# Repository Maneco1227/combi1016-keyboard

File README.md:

# Combi1016-keyboard
Combi1016 keyboard is an additional keyboard, suitable for inputting hexadecimal number.
This keyboard is useful to input a css color code and coordinates on a cad application. 

In this repository, KiCAD schema, PCB layout, gerber and qmk firmware are available.
Their data is **AS IS**, no warranties.

# Key layout
Press Fn key, it changes Normal and Fn(Hex) mode alternately.

## Normal mode

## Fn(Hex) mode

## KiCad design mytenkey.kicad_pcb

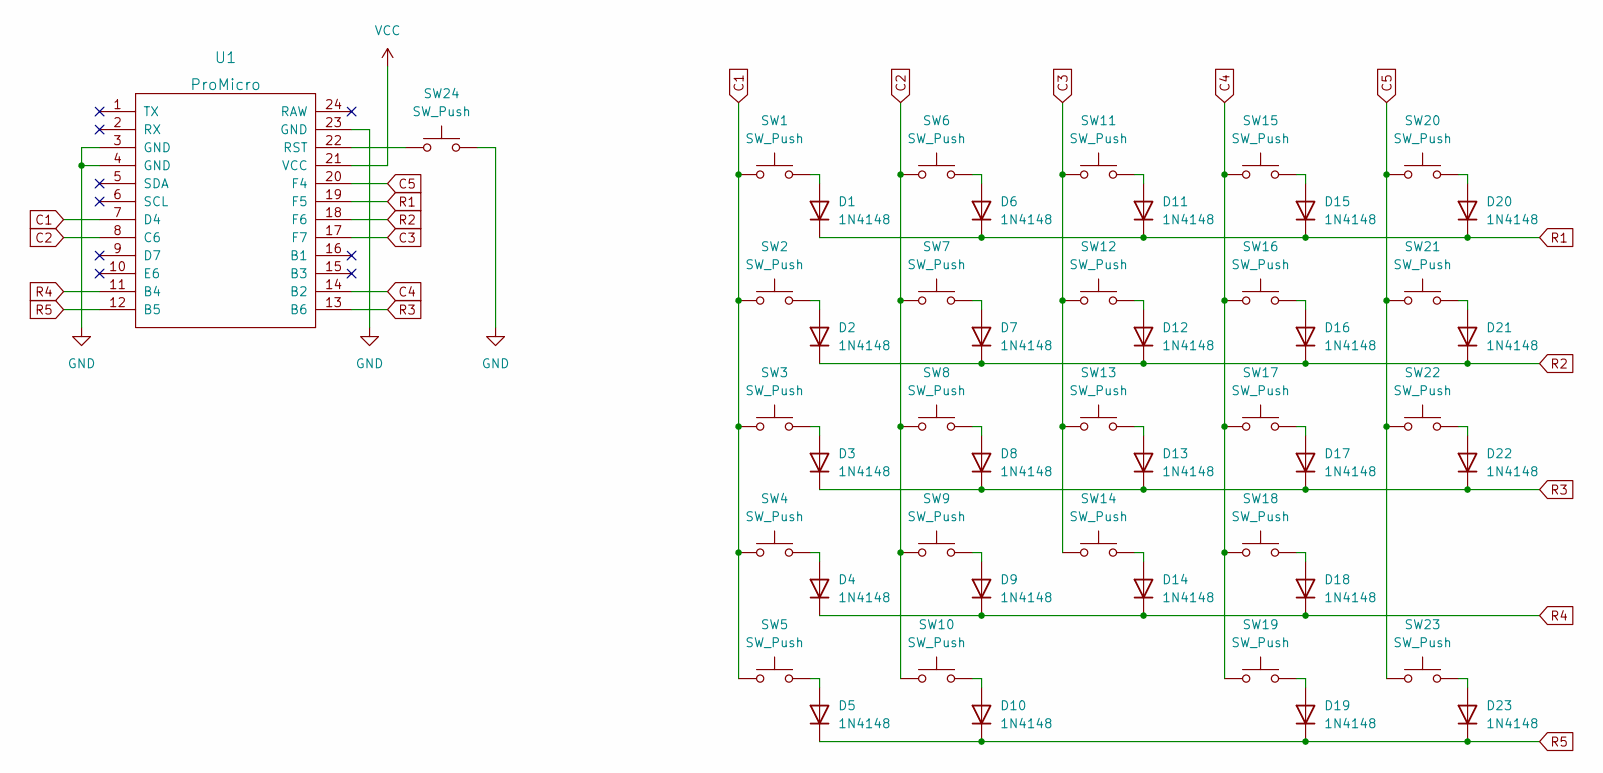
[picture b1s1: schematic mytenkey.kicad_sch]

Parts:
D1, D2, D3, D4, D5, D6, D7, D8, D9, D10, D11, D12, D13, D14, D15, D16, D17, D18, D19, D20, D21, D22, D23: 1N4148; D_DO-35_SOD27_P7.62mm_Horizontal
SW1, SW2, SW3, SW4, SW5, SW6, SW7, SW8, SW9, SW11, SW12, SW13, SW14, SW15, SW16, SW17, SW18, SW19, SW20, SW21, SW22: SW_Push; SW_Cherry_MX_1.00u_PCB
SW10: SW_Push; SW_Cherry_MX_2.00u_PCB
SW23: SW_Push; SW_Cherry_MX_2.00u_Vertical_PCB
SW24: SW_Push
U1: ProMicro

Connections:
C1: SW1.1, SW2.1, SW3.1, SW4.1, SW5.1, U1.7 (D4)
C2: SW6.1, SW7.1, SW8.1, SW9.1, SW10.1, U1.8 (C6)
C3: SW11.1, SW12.1, SW13.1, SW14.1, U1.17 (F7)
C4: SW15.1, SW16.1, SW17.1, SW18.1, SW19.1, U1.14 (B2)
C5: SW20.1, SW21.1, SW22.1, SW23.1, U1.20 (F4)
GND: SW24.2, U1.3 (GND), U1.4 (GND), U1.23 (GND)
unnamed: D1.2 (A), SW1.2
unnamed: D2.2 (A), SW2.2
unnamed: D3.2 (A), SW3.2
unnamed: D4.2 (A), SW4.2
unnamed: D5.2 (A), SW5.2
unnamed: D6.2 (A), SW6.2
unnamed: D7.2 (A), SW7.2
unnamed: D8.2 (A), SW8.2
unnamed: D9.2 (A), SW9.2
unnamed: D10.2 (A), SW10.2
unnamed: D11.2 (A), SW11.2
unnamed: D12.2 (A), SW12.2
unnamed: D13.2 (A), SW13.2
unnamed: D14.2 (A), SW14.2
unnamed: D15.2 (A), SW15.2
unnamed: D16.2 (A), SW16.2
unnamed: D17.2 (A), SW17.2
unnamed: D18.2 (A), SW18.2
unnamed: D19.2 (A), SW19.2
unnamed: D20.2 (A), SW20.2
unnamed: D21.2 (A), SW21.2
unnamed: D22.2 (A), SW22.2
unnamed: D23.2 (A), SW23.2
unnamed: SW24.1, U1.22 (RST)
R1: D1.1 (K), D6.1 (K), D11.1 (K), D15.1 (K), D20.1 (K), U1.19 (F5)
R2: D2.1 (K), D7.1 (K), D12.1 (K), D16.1 (K), D21.1 (K), U1.18 (F6)
R3: D3.1 (K), D8.1 (K), D13.1 (K), D17.1 (K), D22.1 (K), U1.13 (B6)
R4: D4.1 (K), D9.1 (K), D14.1 (K), D18.1 (K), U1.11 (B4)
R5: D5.1 (K), D10.1 (K), D19.1 (K), D23.1 (K), U1.12 (B5)
VCC: U1.21 (VCC)

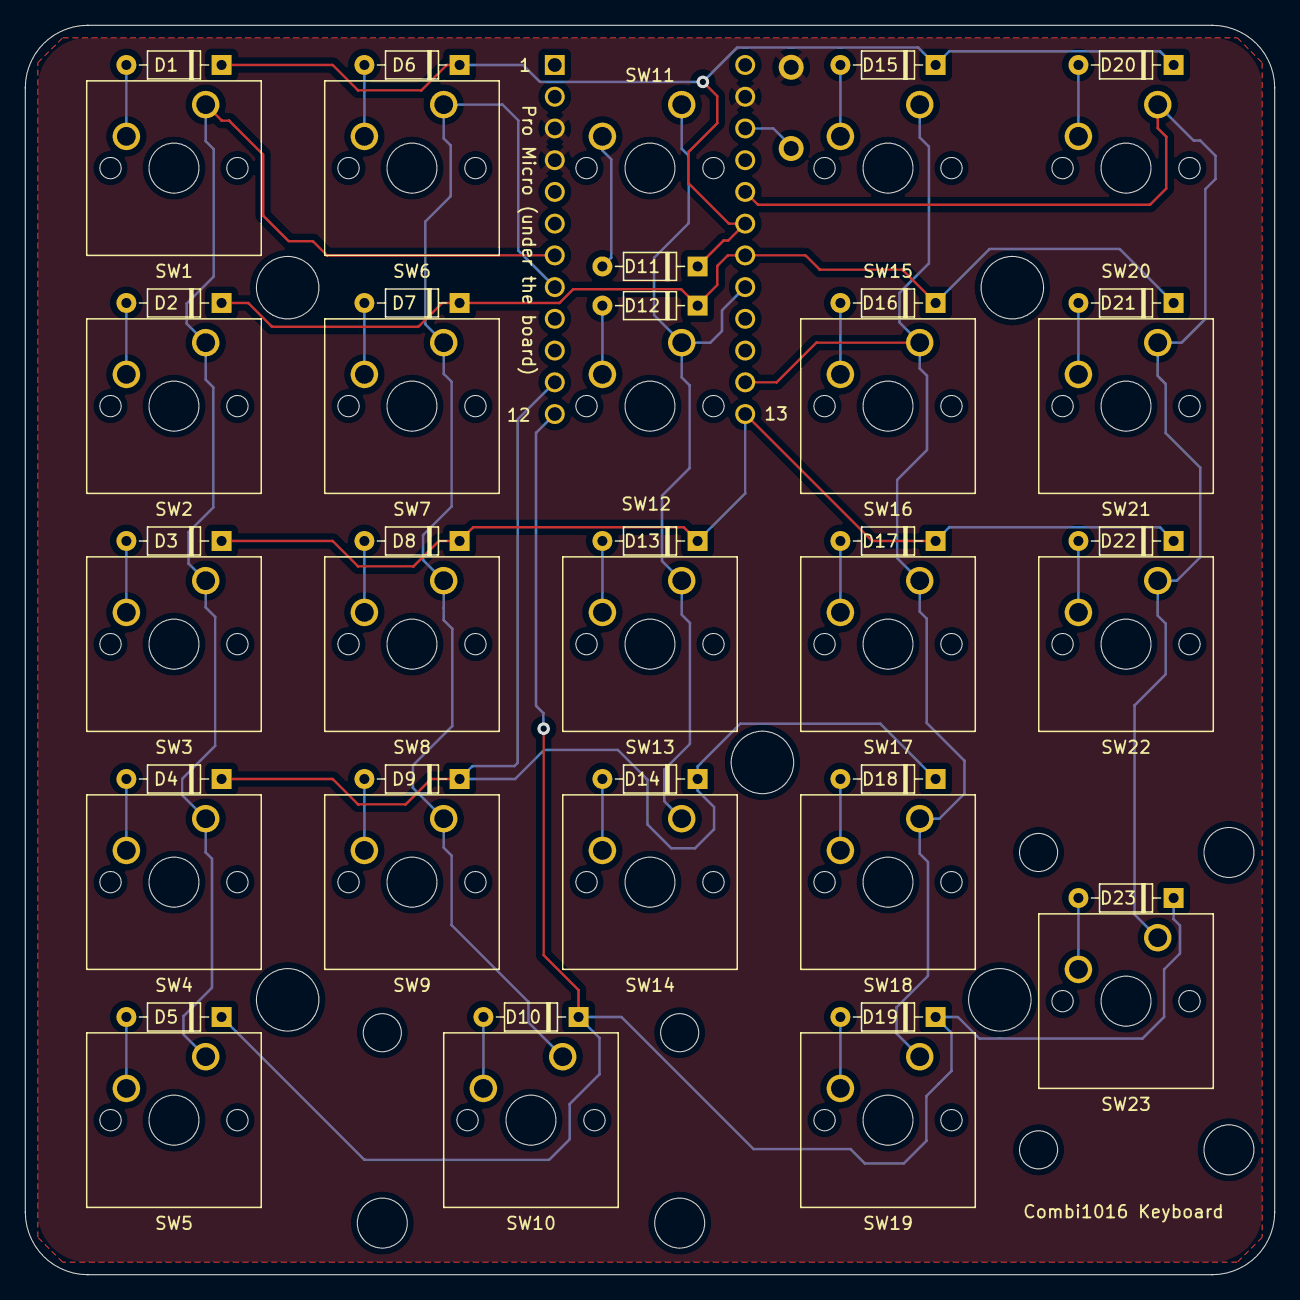
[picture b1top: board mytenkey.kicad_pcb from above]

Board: 2 copper layers, 100.0 x 100.0 mm, 48 parts (1 on the bottom side), 35 nets.
